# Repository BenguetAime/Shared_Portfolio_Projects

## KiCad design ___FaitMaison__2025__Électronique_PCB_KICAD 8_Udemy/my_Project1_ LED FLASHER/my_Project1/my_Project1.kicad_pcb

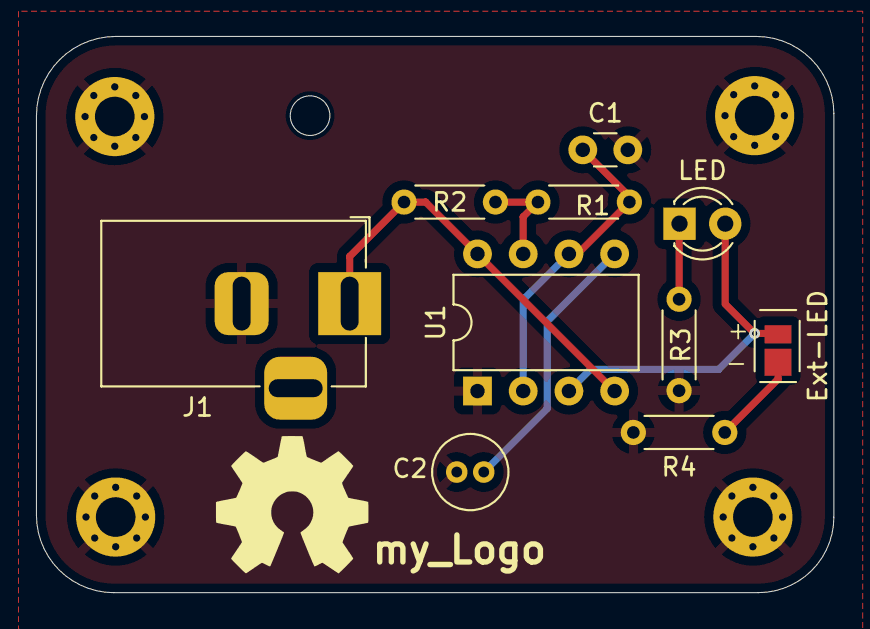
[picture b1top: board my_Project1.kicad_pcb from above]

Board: 2 copper layers, 44.3 x 30.9 mm, 16 parts (0 on the bottom side), 8 nets.

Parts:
C1: 10u; C_Disc_D3.0mm_W1.6mm_P2.50mm
C2: 100n; C_Radial_D4.0mm_H5.0mm_P1.50mm
Ext-LED: External LED; SolderJumper-2_P1.3mm_Open_Pad1.0x1.5mm
H1, H2, H3, H4: MountingHole_Pad; MountingHole_2.2mm_M2_Pad_Via
H5: MountingHole; MountingHole_2.2mm_M2
J1: Barrel_Jack; BarrelJack_Horizontal
LED: LED; LED_D3.0mm
R1: 72k; R_Axial_DIN0204_L3.6mm_D1.6mm_P5.08mm_Horizontal
R2: 150; R_Axial_DIN0204_L3.6mm_D1.6mm_P5.08mm_Horizontal
R3, R4: 2k; R_Axial_DIN0204_L3.6mm_D1.6mm_P5.08mm_Horizontal
U1: NA555P; DIP-8_W7.62mm
my_Logo: LOGO; LED Flasher

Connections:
GND: C1.2, C2.1, H1.1, H2.1, H3.1, H4.1, J1.2, R3.2, R4.2, U1.1 (GND)
unnamed: LED.1 (K), R3.1
unnamed: Ext-LED.1 (A), R4.1
unnamed: C2.2, U1.5 (CV)
unnamed: R1.1, R2.2, U1.7 (DIS)
OUT: Ext-LED.2 (B), LED.2 (A), U1.3 (Q)
TR: C1.1, R1.2, U1.2 (TR), U1.6 (THR)
VDD: J1.1, R2.1, U1.4 (R), U1.8 (VCC)

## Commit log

2024-01-26 chgm1
2024-01-26 camera_ubuntu_config_0.0.0
2024-01-28 camera_update_0.0.1
2024-05-26 com1
2025-01-07 Mise à jour - Github Academic & Personal Projects
    Ce répertoire présente les projets les plus intéressants sur lesquels j'ai travaillé :
    - Projets personnels, fait-maison
    - Projets académiques
    - Stages
2025-01-07 MAJ 1
2025-01-07 Mise à jour - Certifications
2025-01-07 MAJ_01
2025-01-08 Rename Lancer_DRC_DesignRulesCheck__Puis EXECUTER__pour voir si on a oublié un tracé de piste.png to Lancer_DRC.png
